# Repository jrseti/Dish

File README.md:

# Dish Repository

This repository contains hardware and firmware work for refurbishing a legacy
3-meter satellite dish into a modern, networked robotic system.

The design is split into two PCB projects that work together over CAN:

## Projects

### 1. `controller/` - RCM Dish Controller Board

The main motion-control and compute board for the dish.

- STM32-based two-axis motion controller
- On-board Raspberry Pi Compute Module 4 carrier
- Power, I/O, communications, and safety/control interfaces
- KiCad hardware design plus associated embedded/software assets

See: [controller/README.md](controller/README.md)

### 2. `can_hub/` - CAN Bus Hub

A simple CAN distribution hub that also routes 24 V power to CAN_V+ pins.

See: [can_hub/README.md](can_hub/README.md)

## Repository Layout

- `controller/`: Main controller electronics, docs, and software
- `can_hub/`: CAN power/distribution hub hardware

## Purpose

Together, these boards provide the control and field-bus backbone for the dish:

- `controller/` runs motion control and local host integration
- `can_hub/` provides CAN/power fan-out for connected nodes

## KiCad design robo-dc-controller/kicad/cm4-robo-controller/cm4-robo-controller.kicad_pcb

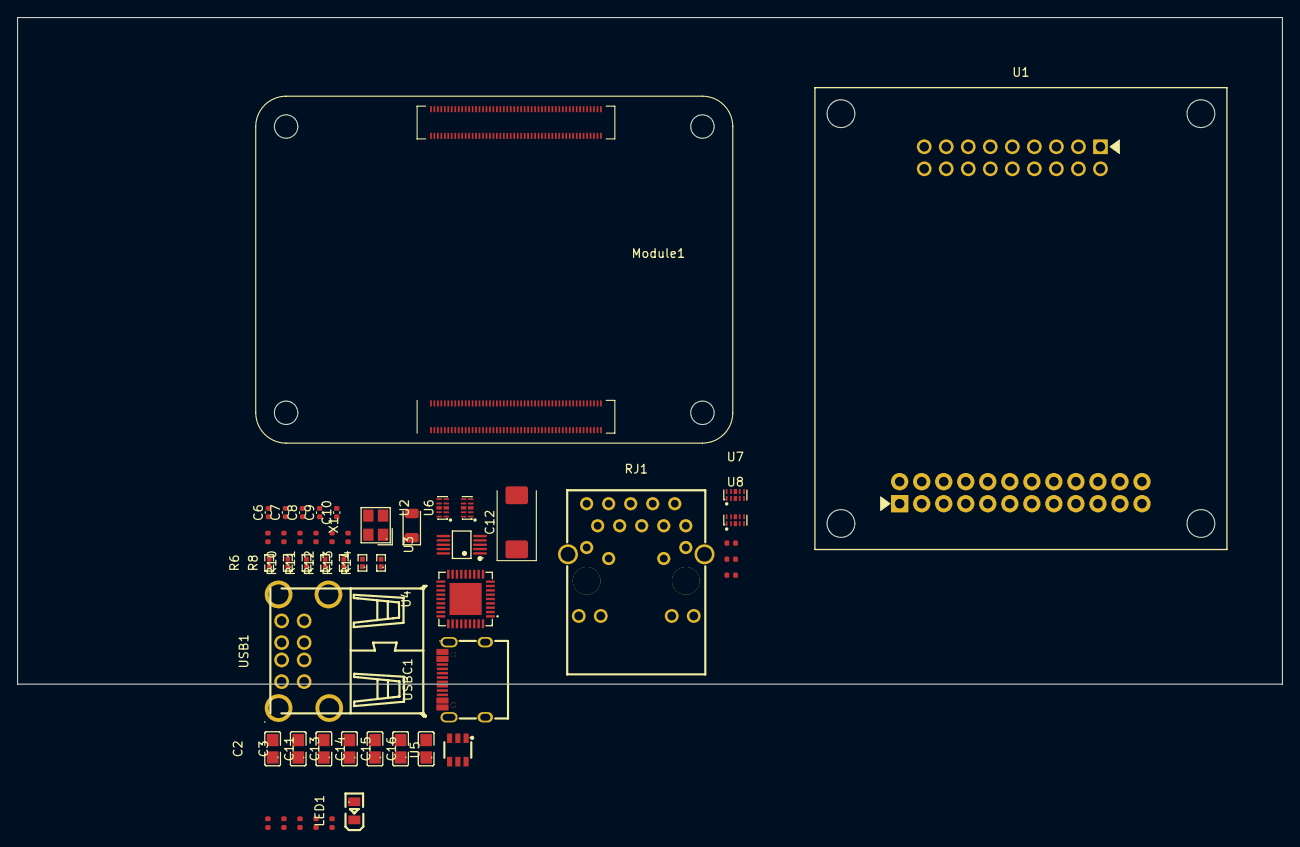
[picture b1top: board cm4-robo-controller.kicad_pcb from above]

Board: 2 copper layers, 145.8 x 76.9 mm, 49 parts (0 on the bottom side), 48 nets, no tracks yet.

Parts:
C1, C4: 15pF; C_0402
C2, C3, C11, C13, C14, C15, C16: 10uF 10V; C0805
C5, C17: 100nF; C_0402
C6, C7, C8, C9, C10: 100n; C_0402_1005Metric
C12: 100uF 6.3V; CP_EIA-7343-31_Kemet-D
D1: SMF6.0A; D_SOD-123FL
LED1: RED; LED0805-R-RD
Module1: ComputeModule4-CM4; Raspberry-Pi-4-Compute-Module
R1: 10kΩ; R_0402
R2, R3, R4: 100Ω; R_0402
R5, R16, R17: 1.5kΩ; R_0402
R6, R8: 2.2kΩ; R0402
R7, R9: 5.1kΩ; R_0402
R10, R11, R13, R14: 36K 1%; R0402
R12: 12kΩ; R0402
R15: 15kΩ; R_0402
RJ1: LPJG0926HENL_C22457393; RJ45-TH_LPJG0926HENL_C22457393
U1: ROBOCLAW-2X15A-OEM; MOD-TH_ROBOCLAW-OEM-2X15A
U2, U6: TPD4EUSB30DQAR-N; DFN-10_L2.5-W1.0-P0.50-BL-A
U3: FSUSB42MUX; MSOP-10_L3.0-W3.0-P0.50-LS5.0-BL
U4: USB2514B-I/M2; SQFN-36_L6.0-W6.0-P0.50-BL-EP
U5: AP22653W6-7; SOT-23-6_L2.9-W1.6-P0.95-LS2.8-BR
U7, U8: TPD4EUSB30DQAR; USON-10_L2.5-W1.0-P0.50-BL
USB1: Double layer DIP 90° black; USB-A-TH_USB-M-51
USBC1: TYPE-C-31-M-12; USB-C_SMD-TYPE-C-31-M-12_1
X1: X322524MOB4SI; CRYSTAL-SMD_4P-L3.2-W2.5-BL

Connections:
3V3_CM4: C2.2, C3.2, C5.1, C6.1, C7.1, C8.1, C9.1, C10.1, Module1.78 (GPIO_VREF(1.8v/3.3v_Input)), Module1.84 (+3.3v_(Output)), Module1.86 (+3.3v_(Output)), R1.1, U3.1 (VCC), U4.5 (VDDA33), U4.10 (VDDA33), U4.15 (VDD33), U4.23 (VDD33), U4.27 (VBUS_DET), U4.29 (VDDA33), U4.36 (VDDA33)
5V: C11.2, LED1.1 (A), Module1.77 (+5v_(Input)), Module1.79 (+5v_(Input)), Module1.81 (+5v_(Input)), Module1.83 (+5v_(Input)), Module1.85 (+5v_(Input)), Module1.87 (+5v_(Input)), RJ1.15, RJ1.17, U5.1 (IN)
/CM4/EP0+: Module1.12 (Ethernet_Pair0_P), RJ1.1 (TD1+), U7.1 (D1+)
/CM4/EP0-: Module1.10 (Ethernet_Pair0_N), RJ1.2 (TD1-), U7.2 (D1-)
/CM4/EP1+: Module1.4 (Ethernet_Pair1_P), RJ1.3 (TD2+), U7.4 (D2+)
/CM4/EP1-: Module1.6 (Ethernet_Pair1_N), RJ1.6 (TD2-), U7.5 (D2-)
/CM4/EP2+: Module1.11 (Ethernet_Pair2_P), RJ1.7 (TD3+), U8.1 (D1+)
/CM4/EP2-: Module1.9 (Ethernet_Pair2_N), RJ1.8 (TD3-), U8.2 (D1-)
/CM4/EP3+: Module1.3 (Ethernet_Pair3_P), RJ1.9 (TD4+), U8.4 (D2+)
/CM4/EP3-: Module1.5 (Ethernet_Pair3_N), RJ1.10 (TD4-), U8.5 (D2-)
/CM4/ETH_LEDG: Module1.17 (Ethernet_nLED2(3.3v)), R16.1
/CM4/ETH_LEDY: Module1.15 (Ethernet_nLED3(3.3v)), R17.2
/CM4/MCU_nIRQ: R1.2, R2.1
/CM4/USB2_N: Module1.103 (USB2_N), U3.4 (D-)
/CM4/USB2_P: Module1.105 (USB2_P), U3.3 (D+)
/CM4/USB_OTG_ID: Module1.101 (USB_OTG_ID), R6.1, R8.1, U3.2 (Sel)
/CM4/nEXTRST: Module1.100 (nEXTRST), U4.26 (RESET_N)
/CM4/usb/HD1_N: U4.1 (USBDM_DN1/PRT_DIS_M1), U6.5, USB1.6 (D-)
/CM4/usb/HD1_P: U4.2 (USBDP_DN1/PRT_DIS_P1), U6.4, USB1.7 (D+)
/CM4/usb/HD2_N: U4.3 (USBDM_DN2/PRT_DIS_M2), U6.2, USB1.2 (D-)
/CM4/usb/HD2_P: U4.4 (USBDP_DN2/PRT_DIS_P2), U6.1, USB1.3 (D+)
/CM4/usb/HSD2+: U2.1, U3.9 (HSD2+), USBC1.A6 (DP1), USBC1.B6 (DP2)
/CM4/usb/HSD2-: U2.2, U3.8 (HSD2-), USBC1.A7 (DN1), USBC1.B7 (DN2)
/CM4/usb/PWR1: U4.12 (PRTPWR1/BC_EN1), U5.3 (EN/~EN)
/CM4/usb/VBUS: C12.1, C13.2, C14.2, C15.2, C16.2, D1.1, U5.6 (OUT), USB1.1 (VCC), USB1.5 (VCC)
/CM4/usb/nOCS1: U4.13 (OCS_N1), U4.17 (OCS_N2), U4.19 (OCS_N3), U4.21 (OCS_N4), U5.4 (~FAULT)
GND: C1.2, C2.1, C3.1, C4.2, C5.2, C6.2, C7.2, C8.2, C9.2, C10.2, C11.1, C12.2, C13.1, C14.1, C15.1, C16.1, C17.2, D1.2, Module1.1 (GND), Module1.2 (GND), Module1.7 (GND), Module1.8 (GND), Module1.13 (GND), Module1.14 (GND), Module1.22 (GND), Module1.23 (GND), Module1.32 (GND), Module1.33 (GND), Module1.42 (GND), Module1.43 (GND), Module1.52 (GND), Module1.53 (GND), Module1.59 (GND), Module1.60 (GND), Module1.65 (GND), Module1.66 (GND), Module1.71 (GND), Module1.74 (GND), Module1.98 (GND), Module1.107 (GND), Module1.108 (GND), Module1.113 (GND), Module1.114 (GND), Module1.119 (GND), Module1.120 (GND), Module1.125 (GND), Module1.126 (GND), Module1.131 (GND), Module1.132 (GND), Module1.137 (GND), Module1.138 (GND), Module1.144 (GND), Module1.150 (GND), Module1.155 (GND), Module1.156 (GND), Module1.161 (GND), Module1.162 (GND), Module1.167 (GND), Module1.168 (GND), Module1.173 (GND), Module1.174 (GND), Module1.179 (GND), Module1.180 (GND), Module1.185 (GND), Module1.186 (GND), Module1.191 (GND), Module1.192 (GND), Module1.197 (GND), Module1.198 (GND), R6.2, R7.2, R9.2, R10.1, R11.1, R12.1, R13.1, R14.1, R15.2, RJ1.19 (EH), RJ1.20 (EH), U2.3, U2.8, U3.5 (GND), U3.10 (~OE), U4.37 (EP), U5.2 (GND), U6.3, U6.8, U7.3 (GND), U7.8 (GND), U8.3 (GND), U8.8 (GND), USB1.4 (GND), USB1.8 (GND), USB1.9, USBC1.1 (EH), USBC1.2 (EH), USBC1.3 (EH), USBC1.4 (EH), USBC1.A1B12 (GND), USBC1.B1A12 (GND), X1.2 (GND), X1.4 (GND)
unnamed: C17.1, RJ1.4 (CT), RJ1.5 (CT)
unnamed: LED1.2 (K), R5.1
unnamed: Module1.54 (GPIO4), R4.2
unnamed: Module1.34 (GPIO5), R3.2
unnamed: Module1.30 (GPIO6), R2.2
unnamed: Module1.21 (PI_nLED_Activity), R5.2
unnamed: R8.2, USBC1.A4B9 (VBUS), USBC1.B4A9 (VBUS)
unnamed: R16.2, RJ1.16
unnamed: R17.1, RJ1.18
unnamed: U3.7 (HSD1+), U4.31 (USBDP_UP)
unnamed: U3.6 (HSD1-), U4.30 (USBDM_UP)
unnamed: R14.2, U4.25 (HS_IND/CFG_SEL1)
unnamed: R12.2, U4.35 (RBIAS)
unnamed: R10.2, U4.24 (SCL/SMBCLK/CFG_SEL0)
unnamed: R11.2, U4.22 (SDA/SMBBATA/NON_REM1)
unnamed: R13.2, U4.28 (SUSP_IND/LOCAL_PWR/NON_REM0)
unnamed: C1.1, U4.33 (XTALIN/CLKIN), X1.1 (OSC1)
unnamed: C4.1, U4.32 (XTALOUT), X1.3 (OSC2)
unnamed: R15.1, U5.5 (ILIM)
unnamed: R7.1, USBC1.A5 (CC1)
unnamed: R9.1, USBC1.B5 (CC2)

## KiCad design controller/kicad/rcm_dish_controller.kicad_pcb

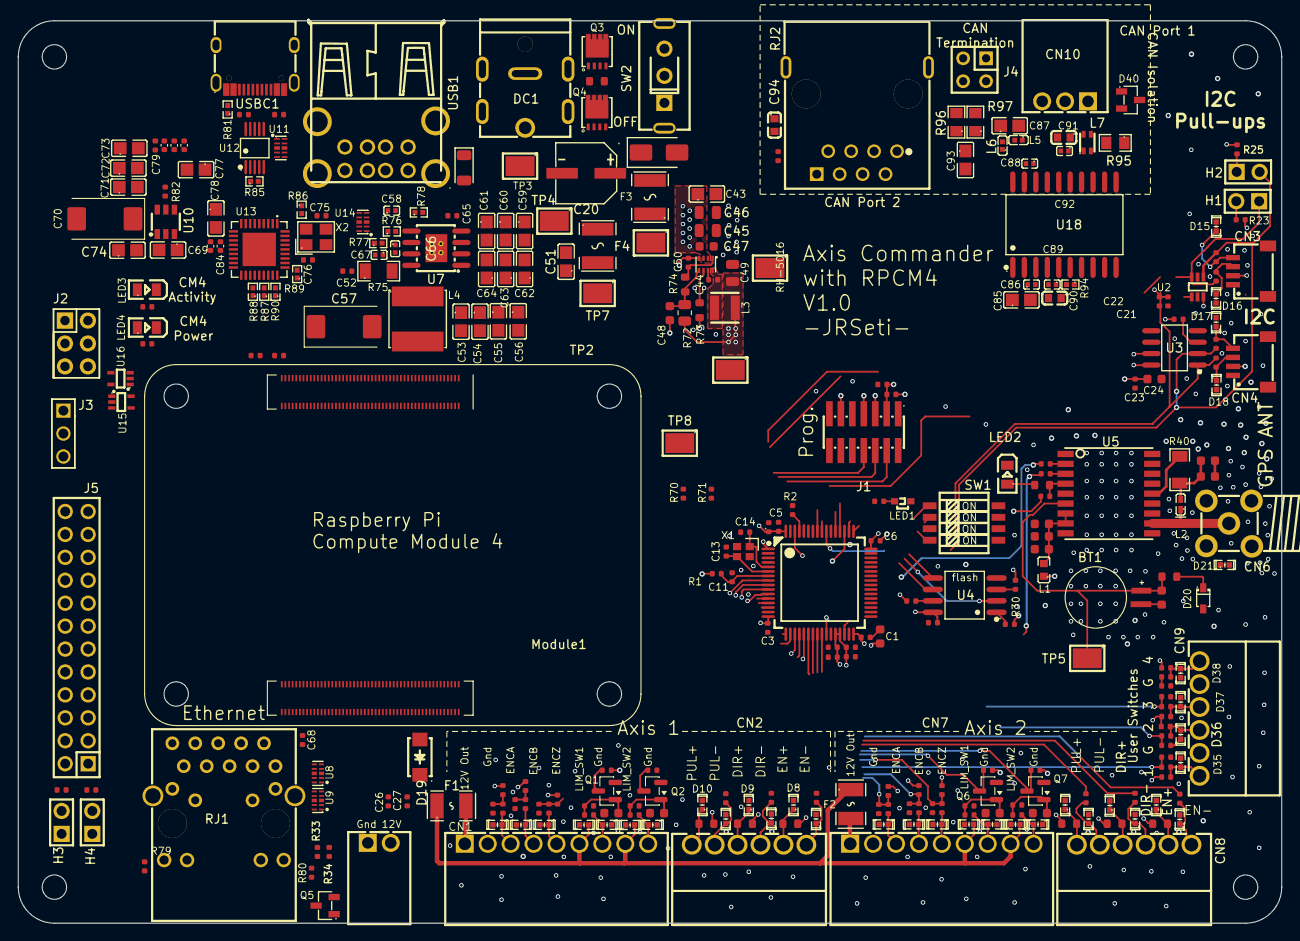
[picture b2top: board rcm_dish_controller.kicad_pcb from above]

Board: 4 copper layers, 140.0 x 100.0 mm, 314 parts (0 on the bottom side), 205 nets.

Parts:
BT1: MS621FE-FL11E; BAT_MS621FE-FL11E
C1: 4.7uF; C_0603
C2, C3, C4, C5, C6, C9, C11, C12, C12#2, C22, C23, C25, C27, C39, C40, C41, C42, C44, C52, C65, C68, C79: 100nF; C_0402
C7, C26: 10nF; C_0402
C8, C10, C50: 1uF; C_0402
C13, C14: 6.8pF; C_0402
C15, C16, C17, C34, C35, C36: 1nF; C_0402
C18, C19, C33, C37, C38: 10nF; C_0603
C20: 220uF; CAP-SMD_BD6.3-L6.6-W6.6-FD
C21: 4.7uF; C_0402
C24, C29: 10uF; C_0603
C28: 1uF; C_0603
C30, C31, C47: 100nF; C_0603
C32: 47pF; C_0603
C43, C51: 100nF; C0805
C45, C46: 10uF; C_0805
C48: 22pF; C_0603
C49: 22uF; C_0805
C53, C54, C55, C56, C69, C71, C72, C73, C74, C77, C78: 10uF 10V; C0805
C57, C70: 100uF 6.3V; CP_EIA-7343-31_Kemet-D
C58, C66: DNP; C0402
C59, C60, C61, C62, C63, C64: 10uF 35V; C0805
C67: 1.2nF; C0402
C75, C76: 15pF; C_0402
C80, C81, C82, C83, C84: 100n; C_0402_1005Metric
C85, C87: 10uF; C0805
C86, C88, C89, C92: 100nF; C0402
C90, C91: 10nF; C0603
C93: 4.7nF; C0805
C94: 1nF; C0603
CN1, CN7: KF2EDGR-2.54-9P; CONN-TH_9P-P2.54_KF2EDGR-2.54-9P
CN2, CN8, CN9: KF2EDGR-2.54-6P; CONN-TH_KF2EDGR-2.54-6P
CN3, CN4: SM04B-SRSS-TB (LF)(SN); CONN-SMD_4P-P1.00_SM04B-SRSS-TB-LF-SN
CN5: KF2EDGR-2.54-2P; CONN-TH_P2.54_KF2EDGR-2.54-2P
CN6: SMA-KWE_C7498154; SMA-TH_SMA-KWE_C7498154
CN10: KF2EDGR-2.54-3P; CONN-TH_3P-P2.54_KF2EDGR-2.54-3P
D1, D2, D3, D8, D9, D10, D11, D12, D13, D15, D16, D17, D18, D22, D23, D24, D29, D30, D31, D32, D33, D34, D35, D36, D37, D38: TPESD0402G05V; D0402-BI
D4, D5, D6, D7, D25, D26, D27, D28: TPESD0402G15V; D0402-BI
D14: SMAJ14A; D_SMA
D19: SS14; SMA_L4.2-W2.6-LS5.0-RD_1
D20: 1N4148WS T4; SOD-323_L1.8-W1.3-LS2.5-RD
D21: PESD0402-140; D0402-BI
D39: SMF6.0A; D_SOD-123FL
D40: NUP2105LT1G; SOT-23-3_L2.9-W1.3-P1.90-LS2.4-BL-2
DC1: DC007B-2.5-J; DC-IN-TH_HX-DC007B-2.5
F1, F2: MF-USMF020-2; F1210
F3: 1812L110/48QR; F1812
F4: SMD1812P300TF/16; F1812
H1, H2, H3, H4: 210S-1*2P L=11.6MMGold-plated black; HDR-TH_2P-P2.54-V-M-1
J1: Conn_ST_STDC14; HDR-SMD_14P-P1.27_FTSH-107-01-L-DV-K
J2: Header-Male-2.54_2x3; HDR-TH_6P-P2.54-V-M-R2-C3-S2.54-1
J3: Header-Male-2.54_1x3; HDR-TH_3P-P2.54-V-M-1
J4: Header-Male-2.54_2x2; HDR-TH_4P-P2.54-V-M-R2-C2-S2.54-1
J5: 2541WV-2X12P; HDR-TH_24P-P2.54-V-M-R2-C12-S2.54
L1: BLM18AG601SN1D; L0603
L2: LQG15HS27NJ02D; L0402-RD
L3: 3.3uH; IND-SMD_L3.0-W3.0-1
L4: SRN6045TA-3R3Y; IND-SMD_L6.0-W6.0
L5, L6: BLM15HD182SN1D; L0402
L7: 370R@100MHz; FILTER-SMD_4P-L2.0-W1.2-BL
LED1: LTST-S270KGKT; LED-SMD_L1.7-W0.6-RD
LED2: XL-0805QBC; LED0805-R-RD
LED3: RED; LED0805-R-RD
LED4: GREEN; LED0805-R-RD
M1, M2, M3, M4: MountingHole_2.7mm_M2.5_ISO14580
Module1: ComputeModule4-CM4; Raspberry-Pi-4-Compute-Module
Q1, Q2, Q6, Q7: BSS138; SOT-23
Q3, Q4: DMP3013SFV-7; DFN-8_L3.3-W3.3-P0.65-BL
Q5: AO3400A; SOT-23-3_L2.9-W1.3-P1.90-LS2.4-BR
R1, R2, R13, R14, R18, R19, R23, R24, R25, R26, R27, R30, R34, R49, R50, R55, R56, R68: 10kΩ; R_0402
R3: 330Ω; R_0402
R4, R5, R6, R38, R41, R42, R43, R91: 1kΩ; R_0402
R7, R8, R9, R11, R15, R17, R33, R35, R36, R44, R45, R46, R48, R52, R54, R60, R62, R64, R66, R69, R70, R71: 100Ω; R_0402
R10, R12, R16, R47, R51, R53: 180Ω; R_0603
R20, R21, R57, R58, R82: 15kΩ; R_0402
R22: 10kΩ; R_0603
R28, R29, R31, R32: 22Ω; R_0402
R37, R39: 1kΩ; R_0603
R40, R75: 10Ω; R1206
R59, R61, R63, R65, R92, R93: 4.7kΩ; R_0402
R67, R79, R80: 1.5kΩ; R_0402
R72: 976kΩ; R_0805_2012Metric
R73: 100kΩ; R_0603
R74: 220kΩ; R_0603
R76, R86: 12kΩ; R0402
R77: 20kΩ; R0402
R78, R81, R85: 2.2kΩ; R0402
R83, R84: 5.1kΩ; R_0402
R87, R88, R89, R90: 36K 1%; R0402
R94: 0Ω; R0402
R95: 47KΩ; R0805
R96, R97: 60.4Ω; R0805
R98: 1MΩ; R_0402
RJ1: LPJG0926HENL_C22457393; RJ45-TH_LPJG0926HENL_C22457393
RJ2: KH-RJ45-58-8P8C; RJ45-TH_KH-RJ45-58-8P8C
SW1: DSHP04TSGER; SW-SMD_8P-L6.7-W5.4-P1.27-LS8.4
SW2: SS-12F49-G050; SW-TH_SS-12F45-GXXX
TP1, TP2, TP3, TP4, TP5, TP6, TP7, TP8: RH-5016; TESTPOINT-SMD_L3.0-W2.0
U1: STM32G474RET6; LQFP-64_L10.0-W10.0-P0.50-LS12.0-BL
U2: LTC4311ISC6#TRPBF; SC-70-6_L2.2-W1.3-P0.65-LS2.2-BL
U3: LM75BIMX-3/NOPB; SOIC-8_L4.9-W3.9-P1.27-LS6.0-BL
U4: W25Q32JVSSIQ_C179173; SOIC-8_L5.3-W5.3-P1.27-LS8.0-BL
U5: MAX-M10S-00B; SMD-18_L10.1-W9.7-P1.10-TL_SKG09F
U6: MP2322GQH-Z; QFN-8_L2.0-W1.5-P0.50-BL
U7: AP64501SP-13; SOIC-8_L4.9-W3.9-P1.27-LS6.0-BL-EP-1
U8, U9: TPD4EUSB30DQAR; USON-10_L2.5-W1.0-P0.50-BL
U10: AP22653W6-7; SOT-23-6_L2.9-W1.6-P0.95-LS2.8-BR
U11, U14: TPD4EUSB30DQAR-N; DFN-10_L2.5-W1.0-P0.50-BL-A
U12: FSUSB42MUX; MSOP-10_L3.0-W3.0-P0.50-LS5.0-BL
U13: USB2514B-I/M2; SQFN-36_L6.0-W6.0-P0.50-BL-EP
U15, U16: 74LVC1G07SE-7; SC-88A_L2.0-W1.3-P0.65-LS2.1-BL
U18: ADM3057EBRWZ-RL; SOIC-20_L13.0-W7.6-P1.27-LS10.3-BL
USB1: Double layer DIP 90° black; USB-A-TH_USB-M-51
USBC1: TYPE-C-31-M-12; USB-C_SMD-TYPE-C-31-M-12_1
X1: NX2016SA-16MHZ-EXS00A-CS07826; CRYSTAL-SMD_4P-L2.0-W1.6-BL
X2: X322524MOB4SI; CRYSTAL-SMD_4P-L3.2-W2.5-BL

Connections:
3V3: C1.1, C2.1, C3.1, C4.1, C5.1, C6.1, C7.1, C8.1, C9.1, C10.1, C12.1, C12#2.1, C21.1, C22.1, C23.1, C24.1, C25.1, C48.1, C49.1, C89.2, C90.2, CN3.2, CN4.2, D20.2 (A), J1.3 (VCC), L1.1, L3.2, R1.1, R4.1, R5.1, R6.1, R10.1, R12.1, R13.1, R14.1, R16.1, R23.1, R24.2, R25.1, R26.1, R27.1, R30.1, R41.1, R42.1, R43.1, R47.1, R49.1, R50.1, R51.1, R53.1, R59.1, R61.1, R63.1, R65.1, R72.1, TP1.1 (1_1), U1.1 (VBAT), U1.16 (VDD), U1.28 (VREF+), U1.29 (VDDA), U1.32 (VDD), U1.48 (VDD), U1.64 (VDD), U2.1 (VCC), U2.3 (ENABLE), U3.7 (A0), U3.8 (+VS), U4.8 (VCC), U15.5 (VCC), U18.4 (VIO)
3V3_CM4: C77.2, C78.2, C79.1, C80.1, C81.1, C82.1, C83.1, C84.1, J5.7, LED4.1 (A), Module1.78 (GPIO_VREF(1.8v/3.3v_Input)), Module1.84 (+3.3v_(Output)), Module1.86 (+3.3v_(Output)), R68.1, R92.1, R93.1, U12.1 (VCC), U13.5 (VDDA33), U13.10 (VDDA33), U13.15 (VDD33), U13.23 (VDD33), U13.27 (VBUS_DET), U13.29 (VDDA33), U13.36 (VDDA33), U16.5 (VCC)
5V: C53.2, C54.2, C55.2, C56.2, C57.1, C58.1, C69.2, C85.2, C86.2, J5.5, L4.2, LED3.1 (A), Module1.77 (+5v_(Input)), Module1.79 (+5v_(Input)), Module1.81 (+5v_(Input)), Module1.83 (+5v_(Input)), Module1.85 (+5v_(Input)), Module1.87 (+5v_(Input)), R76.1, RJ1.15, RJ1.17, TP8.1 (1_1), U10.1 (IN), U18.3 (VCC)
12V: C20.1, C26.1, C27.1, CN1.6, CN1.8, CN5.1, CN7.6, CN7.8, D4.2, D6.2, D14.1, D19.1 (K), D25.2, D27.2, F1.1, F2.1, F3.1, F4.1, Q4.5 (D), TP4.1 (1_1)
/1PPS_MCU: Module1.29 (GPIO16), R38.1, U1.62 (PB9)
/Axis Control - 1/12VENC: CN1.1, F1.2
/Axis Control - 1/ENC1_A: CN1.3, D1.1 (K), R7.1
/Axis Control - 1/ENC1_B: CN1.4, D2.1 (K), R8.1
/Axis Control - 1/ENC1_Z: CN1.5, D3.1 (K), R9.1
/Axis Control - 1/LIM1_SW1_RETURN: CN1.7, D5.2, R18.2
/Axis Control - 1/LIM1_SW2_RETURN: CN1.9, D7.2, R19.2
/Axis Control - 2/12VENC: CN7.1, F2.2
/Axis Control - 2/DIR2+: CN8.3, D30.1 (K), R51.2
/Axis Control - 2/DIR2-: CN8.4, D33.1 (K), R52.2
/Axis Control - 2/ENABLE2+: CN8.5, D29.1 (K), R53.2
/Axis Control - 2/ENABLE2-: CN8.6, D34.1 (K), R54.2
/Axis Control - 2/ENC2_A: CN7.3, D22.1 (K), R44.1
/Axis Control - 2/ENC2_B: CN7.4, D23.1 (K), R45.1
/Axis Control - 2/ENC2_Z: CN7.5, D24.1 (K), R46.1
/Axis Control - 2/LIM2_SW1_RETURN: CN7.7, D26.2, R55.2
/Axis Control - 2/LIM2_SW2_RETURN: CN7.9, D28.2, R56.2
/Axis Control - 2/PUL2+: CN8.1, D31.1 (K), R47.2
/Axis Control - 2/PUL2-: CN8.2, D32.1 (K), R48.2
/CAN/CANH: CN10.2, D40.1, J4.1, L7.4, RJ2.1
/CAN/CANHL_C: C93.1, R96.1, R97.1
/CAN/CANH_T: J4.2, R97.2
/CAN/CANL: CN10.1, D40.2, J4.3, L7.3, RJ2.2
/CAN/CANL_T: J4.4, R96.2
/CAN/CAN_SHLD: C94.2, R98.1, RJ2.9, RJ2.10
/CAN/CH: L7.1, U18.14 (CANH)
/CAN/CL: L7.2, U18.13 (CANL)
/CAN/RS: R95.2, U18.12 (RS)
/CAN/RXD: R94.2, U18.5 (RXD)
/CAN/VISOIN: C87.2, C91.2, C92.2, L5.2, U18.16 (VISOIN)
/CAN_RX: R94.1, U1.45 (PA11)
/CAN_TX: U1.46 (PA12), U18.7 (TXD)
/CM4_RX: R71.1, U1.60 (PB7)
/CM4_TX: R70.1, U1.59 (PB6)
/DIR1_MCU: R15.1, U1.22 (PC4)
/DIR2_MCU: R52.1, U1.25 (PB1)
/ENABLE1_MCU: R17.1, U1.23 (PC5)
/ENABLE2_MCU: R54.1, U1.26 (PB2)
/ENC1_A_MCU: C15.1, R4.2, R7.2, U1.12 (PA0)
/ENC1_B_MCU: C16.1, R5.2, R8.2, U1.13 (PA1)
/ENC1_Z_MCU: C17.1, R6.2, R9.2, U1.14 (PA2)
/ENC2_A_MCU: C34.1, R41.2, R44.2, U1.8 (PC0)
/ENC2_B_MCU: C35.1, R42.2, R45.2, U1.9 (PC1)
/ENC2_Z_MCU: C36.1, R43.2, R46.2, U1.11 (PC3)
/FAN_MCU: R33.1, R34.1, U1.57 (PB4)
/FLASH_CS_MCU: R26.2, U1.34 (PB12), U4.1 (~CS)
/GPS/RF_IN: CN6.5, D21.2, L2.1, U5.11 (RF_IN)
/GPS/TIMEPULSE: R38.2, R39.1, U5.4 (TIMEPULSE)
/GPS/VCC: C29.1, C30.1, C31.1, L1.2, U5.7 (V_IO), U5.8 (VCC)
/GPS/VCC_RF: R40.2, U5.14 (VCC_RF)
/GPS/V_BCKP: BT1.+, C28.1, R37.2, TP5.1 (1_1), U5.6 (V_BCKP)
/GPS_RX_MCU: R35.1, U1.30 (PB10)
/GPS_TX_MCU: R36.1, U1.33 (PB11)
/I2C and EEPROM/OS: R24.1, U3.3 (OS)
/I2C and EEPROM/SCL: CN3.4, D15.1 (K), R28.2
/I2C and EEPROM/SDA: CN3.3, D16.1 (K), R31.2
/LIMIT1_SW1_MCU: Q1.3 (D), R13.2, U1.17 (PA3)
/LIMIT1_SW2_MCU: Q2.3 (D), R14.2, U1.18 (PA4)
/LIMIT2_SW1_MCU: Q6.3 (D), R49.2, U1.19 (PA5)
/LIMIT2_SW2_MCU: Q7.3 (D), R50.2, U1.21 (PA7)
/MCU_nIRQ: R68.2, R69.1, U1.55 (PD2)
/NRST: C11.1, J1.12 (~RST), R1.2, U1.7 (PG10-NRST)
/OSC_IN: C14.2, U1.5 (PF0-OSC_IN), X1.1
/OSC_OUT: C13.1, U1.6 (PF1-OSC_OUT), X1.3
/PUL1_MCU: R11.1, U1.20 (PA6)
/PUL2_MCU: R48.1, U1.24 (PB0)
/Power/12V_IN: DC1.1, Q3.5 (D), TP3.1 (1_1)
/Power/Power_3V3/12V_MCU: C43.1, C45.1, C46.1, C47.1, F3.2, TP6.1 (1_1), U6.2 (IN), U6.3 (EN)
/Power/Power_5V/12V_CM4: C51.1, C59.2, C60.2, C61.2, C62.2, C63.2, C64.2, F4.2, TP7.1 (1_1), U7.2 (VIN), U7.3 (EN)
/RCM4/AIN0: J5.2, Module1.96 (AnalogIP0)
/RCM4/AIN1: J5.4, Module1.94 (AnalogIP1)
/RCM4/BOOT_CONSOLE_RXD: J3.1, Module1.51 (GPIO15)
/RCM4/BOOT_CONSOLE_TXD: J3.2, Module1.55 (GPIO14)
/RCM4/EEPROM_nWP: J2.4, Module1.20 (EEPROM_nWP)
/RCM4/EP0+: Module1.12 (Ethernet_Pair0_P), RJ1.1 (TD1+), U8.1 (D1+)
/RCM4/EP0-: Module1.10 (Ethernet_Pair0_N), RJ1.2 (TD1-), U8.2 (D1-)
/RCM4/EP1+: Module1.4 (Ethernet_Pair1_P), RJ1.3 (TD2+), U8.4 (D2+)
/RCM4/EP1-: Module1.6 (Ethernet_Pair1_N), RJ1.6 (TD2-), U8.5 (D2-)
/RCM4/EP2+: Module1.11 (Ethernet_Pair2_P), RJ1.7 (TD3+), U9.1 (D1+)
/RCM4/EP2-: Module1.9 (Ethernet_Pair2_N), RJ1.8 (TD3-), U9.2 (D1-)
/RCM4/EP3+: Module1.3 (Ethernet_Pair3_P), RJ1.9 (TD4+), U9.4 (D2+)
/RCM4/EP3-: Module1.5 (Ethernet_Pair3_N), RJ1.10 (TD4-), U9.5 (D2-)
/RCM4/ETH_LEDG: Module1.17 (Ethernet_nLED2(3.3v)), R79.1
/RCM4/ETH_LEDY: Module1.15 (Ethernet_nLED3(3.3v)), R80.2
/RCM4/GLOBAL_EN: J2.6, Module1.99 (Global_EN)
/RCM4/GPIO22: J5.24, Module1.46 (GPIO22)
/RCM4/I2C1_SCL: H4.1, J5.18, Module1.56 (GPIO3)
/RCM4/I2C1_SDA: H3.1, J5.16, Module1.58 (GPIO2)
/RCM4/PWM0: J5.20, Module1.31 (GPIO12)
/RCM4/PWM1: J5.22, Module1.28 (GPIO13)
/RCM4/RUN_PG: Module1.92 (RUN_PG), U15.2 (A)
/RCM4/SPI0_CE0: J5.12, Module1.39 (GPIO8)
/RCM4/SPI0_CE1: J5.14, Module1.37 (GPIO7)
/RCM4/SPI0_MISO: J5.10, Module1.40 (GPIO9)
/RCM4/SPI0_MOSI: J5.8, Module1.44 (GPIO10)
/RCM4/SPI0_SCLK: J5.6, Module1.38 (GPIO11)
/RCM4/USB2_N: Module1.103 (USB2_N), U12.4 (D-)
/RCM4/USB2_P: Module1.105 (USB2_P), U12.3 (D+)
/RCM4/USB_OTG_ID: Module1.101 (USB_OTG_ID), R81.1, R85.1, U12.2 (Sel)
/RCM4/nEXTRST: Module1.100 (nEXTRST), U13.26 (RESET_N)
/RCM4/nPWR_LED: Module1.95 (nPI_LED_PWR), U16.2 (A)
/RCM4/nRPIBOOT: J2.2, Module1.93 (nRPIBOOT)
/RCM4/usb/HD1_N: U13.1 (USBDM_DN1/PRT_DIS_M1), U14.5, USB1.6 (D-)
/RCM4/usb/HD1_P: U13.2 (USBDP_DN1/PRT_DIS_P1), U14.4, USB1.7 (D+)
/RCM4/usb/HD2_N: U13.3 (USBDM_DN2/PRT_DIS_M2), U14.2, USB1.2 (D-)
/RCM4/usb/HD2_P: U13.4 (USBDP_DN2/PRT_DIS_P2), U14.1, USB1.3 (D+)
/RCM4/usb/HSD2+: U11.1, U12.9 (HSD2+), USBC1.A6 (DP1), USBC1.B6 (DP2)
/RCM4/usb/HSD2-: U11.2, U12.8 (HSD2-), USBC1.A7 (DN1), USBC1.B7 (DN2)
/RCM4/usb/PWR1: U10.3 (EN/~EN), U13.12 (PRTPWR1/BC_EN1)
/RCM4/usb/VBUS: C70.1, C71.2, C72.2, C73.2, C74.2, D39.1, U10.6 (OUT), USB1.1 (VCC), USB1.5 (VCC)
/RCM4/usb/nOCS1: U10.4 (~FAULT), U13.13 (OCS_N1), U13.17 (OCS_N2), U13.19 (OCS_N3), U13.21 (OCS_N4)
/SCL_MCU: H2.2, R28.1, R29.1, U1.38 (PC6), U2.4 (BUS2), U3.2 (SCL)
/SDA_MCU: H1.1, R31.1, R32.1, U1.39 (PC7), U2.6 (BUS1), U3.1 (SDA)
/SPI2_MISO_MCU: U1.36 (PB14), U4.2 (DO(IO1))
/SPI2_MOSI_MCU: U1.37 (PB15), U4.5 (DI(IO0))
/SPI2_SCK_MCU: U1.35 (PB13), U4.6 (CLK)
/STATUS_LED: R3.1, U1.53 (PC11)
/SW1: SW1.1 (A1), U1.52 (PC10)
/SW2: SW1.2 (A2), U1.44 (PA10)
/SW3: SW1.3 (A3), U1.43 (PA9)
/SW4: SW1.4 (A4), U1.42 (PA8)
/SWCLK: J1.6 (JCLK/SWCLK), U1.50 (PA14)
/SWDIO: J1.4 (JTMS/SWDIO), U1.49 (PA13)
/SWO: J1.8 (JTDO/SWO), U1.56 (PB3)
/USER_SW_1_MCU: C39.1, R60.2, U1.10 (PC2)
/USER_SW_2_MCU: C40.1, R62.2, U1.40 (PC8)
/USER_SW_3_MCU: C41.1, R64.2, U1.41 (PC9)
/USER_SW_4_MCU: C42.1, R66.2, U1.51 (PA15)
/User Switches/USER_SW_1: CN9.1, D35.1 (K), R59.2, R60.1
/User Switches/USER_SW_2: CN9.3, D36.1 (K), R61.2, R62.1
/User Switches/USER_SW_3: CN9.4, D37.1 (K), R63.2, R64.1
/User Switches/USER_SW_4: CN9.6, D38.1 (K), R65.2, R66.1
CAN_GND: C87.1, C91.1, C92.1, C93.2, C94.1, CN10.3, D40.3, L6.2, R95.1, R98.2, RJ2.3, U18.11 (GND2), U18.15 (GND2)
CAN_GNDISO: C88.1, L6.1, U18.18 (GNDISO), U18.20 (GNDISO)
GND: BT1.-, C1.2, C2.2, C3.2, C4.2, C5.2, C6.2, C7.2, C8.2, C9.2, C10.2, C11.2, C12.2, C12#2.2, C13.2, C14.1, C15.2, C16.2, C17.2, C18.2, C19.2, C20.2, C21.2, C22.2, C23.2, C24.2, C25.2, C26.2, C27.2, C28.2, C29.2, C30.2, C31.2, C32.2, C33.2, C34.2, C35.2, C36.2, C37.2, C38.2, C39.2, C40.2, C41.2, C42.2, C43.2, C45.2, C46.2, C47.2, C49.2, C50.2, C51.2, C53.1, C54.1, C55.1, C56.1, C57.2, C59.1, C60.1, C61.1, C62.1, C63.1, C64.1, C65.2, C66.2, C67.1, C68.2, C69.1, C70.2, C71.1, C72.1, C73.1, C74.1, C75.2, C76.2, C77.1, C78.1, C79.2, C80.2, C81.2, C82.2, C83.2, C84.2, C85.1, C86.1, C89.1, C90.1, CN1.2, CN3.1, CN3.5, CN3.6, CN4.1, CN4.5, CN4.6, CN6.1, CN6.2, CN6.3, CN6.4, CN7.2, CN9.2, CN9.5, D1.2 (A), D2.2 (A), D3.2 (A), D4.1, D5.1, D6.1, D7.1, D8.2 (A), D9.2 (A), D10.2 (A), D11.2 (A), D12.2 (A), D13.2 (A), D14.2, D15.2 (A), D16.2 (A), D17.2 (A), D18.2 (A), D21.1, D22.2 (A), D23.2 (A), D24.2 (A), D25.1, D26.1, D27.1, D28.1, D29.2 (A), D30.2 (A), D31.2 (A), D32.2 (A), D33.2 (A), D34.2 (A), D35.2 (A), D36.2 (A), D37.2 (A), D38.2 (A), D39.2, DC1.2, DC1.3, J1.5 (GND), J1.7 (GND), J1.11 (GNDDetect), J2.1, J2.3, J3.3, J5.1, J5.3, J5.9, J5.11, J5.13, J5.15, J5.17, J5.19, J5.21, J5.23, LED1.1 (K), LED2.2 (K), Module1.1 (GND), Module1.2 (GND), Module1.7 (GND), Module1.8 (GND), Module1.13 (GND), Module1.14 (GND), Module1.22 (GND), Module1.23 (GND), Module1.32 (GND), Module1.33 (GND), Module1.42 (GND), Module1.43 (GND), Module1.52 (GND), Module1.53 (GND), Module1.59 (GND), Module1.60 (GND), Module1.65 (GND), Module1.66 (GND), Module1.71 (GND), Module1.74 (GND), Module1.98 (GND), Module1.107 (GND), Module1.108 (GND), Module1.113 (GND), Module1.114 (GND), Module1.119 (GND), Module1.120 (GND), Module1.125 (GND), Module1.126 (GND), Module1.131 (GND), Module1.132 (GND), Module1.137 (GND), Module1.138 (GND), Module1.144 (GND), Module1.150 (GND), Module1.155 (GND), Module1.156 (GND), Module1.161 (GND), Module1.162 (GND), Module1.167 (GND), Module1.168 (GND), Module1.173 (GND), Module1.174 (GND), Module1.179 (GND), Module1.180 (GND), Module1.185 (GND), Module1.186 (GND), Module1.191 (GND), Module1.192 (GND), Module1.197 (GND), Module1.198 (GND), Q1.2 (S), Q2.2 (S), Q3.4 (G), Q5.2 (S), Q6.2 (S), Q7.2 (S), R2.1, R20.2, R21.2, R34.2, R57.2, R58.2, R74.2, R78.2, R82.2, R83.2, R84.2, R85.2, R86.1, R87.1, R88.1, R89.1, R90.1, RJ1.19 (EH), RJ1.20 (EH), SW1.5 (B4), SW1.6 (B3), SW1.7 (B2), SW1.8 (B1), SW2.3, TP2.1 (1_1), U1.15 (VSS), U1.27 (VSSA), U1.31 (VSS), U1.47 (VSS), U1.63 (VSS), U2.2 (GND), U2.5 (GND), U3.4 (GND), U3.5 (A2), U3.6 (A1), U4.4 (GND), U5.1 (GND), U5.10 (GND), U5.12 (GND), U6.1 (GND), U7.7 (GND), U7.9 (EP), U8.3 (GND), U8.8 (GND), U9.3 (GND), U9.8 (GND), U10.2 (GND), U11.3, U11.8, U12.5 (GND), U12.10 (~OE), U13.37 (EP), U14.3, U14.8, U15.3 (GND), U16.3 (GND), U18.1 (GND1), U18.2 (GND1), U18.9 (AUXIN), U18.10 (GND1), USB1.4 (GND), USB1.8 (GND), USB1.9, USBC1.1 (EH), USBC1.2 (EH), USBC1.3 (EH), USBC1.4 (EH), USBC1.A1B12 (GND), USBC1.B1A12 (GND), X1.2 (GND), X1.4 (GND), X2.2 (GND), X2.4 (GND)
unnamed: C32.1, C33.1, L2.2, R40.1
unnamed: C52.1, R75.1
unnamed: C67.2, R77.2
unnamed: C68.1, RJ1.4 (CT), RJ1.5 (CT)
unnamed: CN2.5, D8.1 (K), R16.2
unnamed: CN2.3, D9.1 (K), R12.2
unnamed: CN2.1, D10.1 (K), R10.2
unnamed: CN2.2, D11.1 (K), R11.2
unnamed: CN2.4, D12.1 (K), R15.2
unnamed: CN2.6, D13.1 (K), R17.2
unnamed: CN4.4, D17.1 (K), R29.2
unnamed: CN4.3, D18.1 (K), R32.2
unnamed: CN5.2, D19.2 (A), Q5.3 (D)
unnamed: D20.1 (K), R37.1
unnamed: H1.2, R23.2
unnamed: H2.1, R25.2
unnamed: H3.2, R92.2
unnamed: H4.2, R93.2
unnamed: LED1.2 (A), R3.2
unnamed: LED2.1 (A), R39.2
unnamed: LED3.2 (K), R67.1
unnamed: LED4.2 (K), R91.1
unnamed: Module1.54 (GPIO4), R71.2
unnamed: Module1.34 (GPIO5), R70.2
unnamed: Module1.30 (GPIO6), R69.2
unnamed: Module1.21 (PI_nLED_Activity), R67.2
unnamed: C18.1, Q1.1 (G), R18.1, R20.1
unnamed: C19.1, Q2.1 (G), R19.1, R21.1
unnamed: Q3.1 (S), Q3.2 (S), Q3.3 (S), Q4.1 (S), Q4.2 (S), Q4.3 (S), R22.1
unnamed: Q4.4 (G), R22.2, SW2.2
unnamed: Q5.1 (G), R33.2
unnamed: C37.1, Q6.1 (G), R55.1, R57.1
unnamed: C38.1, Q7.1 (G), R56.1, R58.1
unnamed: R79.2, RJ1.16
unnamed: R80.1, RJ1.18
unnamed: R81.2, USBC1.A4B9 (VBUS), USBC1.B4A9 (VBUS)
unnamed: R2.2, U1.61 (PB8-BOOT0)
unnamed: R27.2, U4.7 (I03)
unnamed: R30.2, U4.3 (WP#(IO2))
unnamed: R36.2, U5.3 (RXD)
unnamed: R35.2, U5.2 (TXD)
unnamed: C44.2, U6.7 (BST)
unnamed: C48.2, R72.2, R74.1, U6.5 (FB)
unnamed: R73.1, U6.6 (PG)
unnamed: C44.1, L3.1, U6.8 (SW)
unnamed: C50.1, R73.2, U6.4 (VCC)
unnamed: C52.2, U7.1 (BST)
unnamed: C66.1, R77.1, U7.6 (COMP)
unnamed: C58.2, R76.2, R78.1, U7.5 (FB)
unnamed: C65.1, U7.4 (SS)
unnamed: L4.1, R75.2, U7.8 (SW)
unnamed: R82.1, U10.5 (ILIM)
unnamed: U12.7 (HSD1+), U13.31 (USBDP_UP)
unnamed: U12.6 (HSD1-), U13.30 (USBDM_UP)
unnamed: R90.2, U13.25 (HS_IND/CFG_SEL1)
unnamed: R86.2, U13.35 (RBIAS)
unnamed: R87.2, U13.24 (SCL/SMBCLK/CFG_SEL0)
unnamed: R88.2, U13.22 (SDA/SMBBATA/NON_REM1)
unnamed: R89.2, U13.28 (SUSP_IND/LOCAL_PWR/NON_REM0)
unnamed: C76.1, U13.33 (XTALIN/CLKIN), X2.1 (OSC1)
unnamed: C75.1, U13.32 (XTALOUT), X2.3 (OSC2)
unnamed: J2.5, U15.4 (Y)
unnamed: R91.2, U16.4 (Y)
unnamed: C88.2, L5.1, U18.19 (VISOOUT)
unnamed: R83.1, USBC1.A5 (CC1)
unnamed: R84.1, USBC1.B5 (CC2)

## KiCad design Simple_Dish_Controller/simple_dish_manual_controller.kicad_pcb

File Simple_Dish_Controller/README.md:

# Simple-Dish-Controller
Simple controller with toggle switches to move the motors of a satellite dish.

The project is to create a PCB that will control 2 motors that will be used as the azimuth and elevation motors of a satellite dish. The direction will allow controlling simple movement for each motor, forward, reverse, still, all at one set speed.

The project uses Kicad to create the schematic, PCB and BOM.

This project fulfills 2 initiatives:
- Test out motor control
- Master Kicad for future projects
- Be the base for a follow up PCB that will use a Rashberry Pi to control the motors

## Project Overview

This diagram simply shows the function of the project:

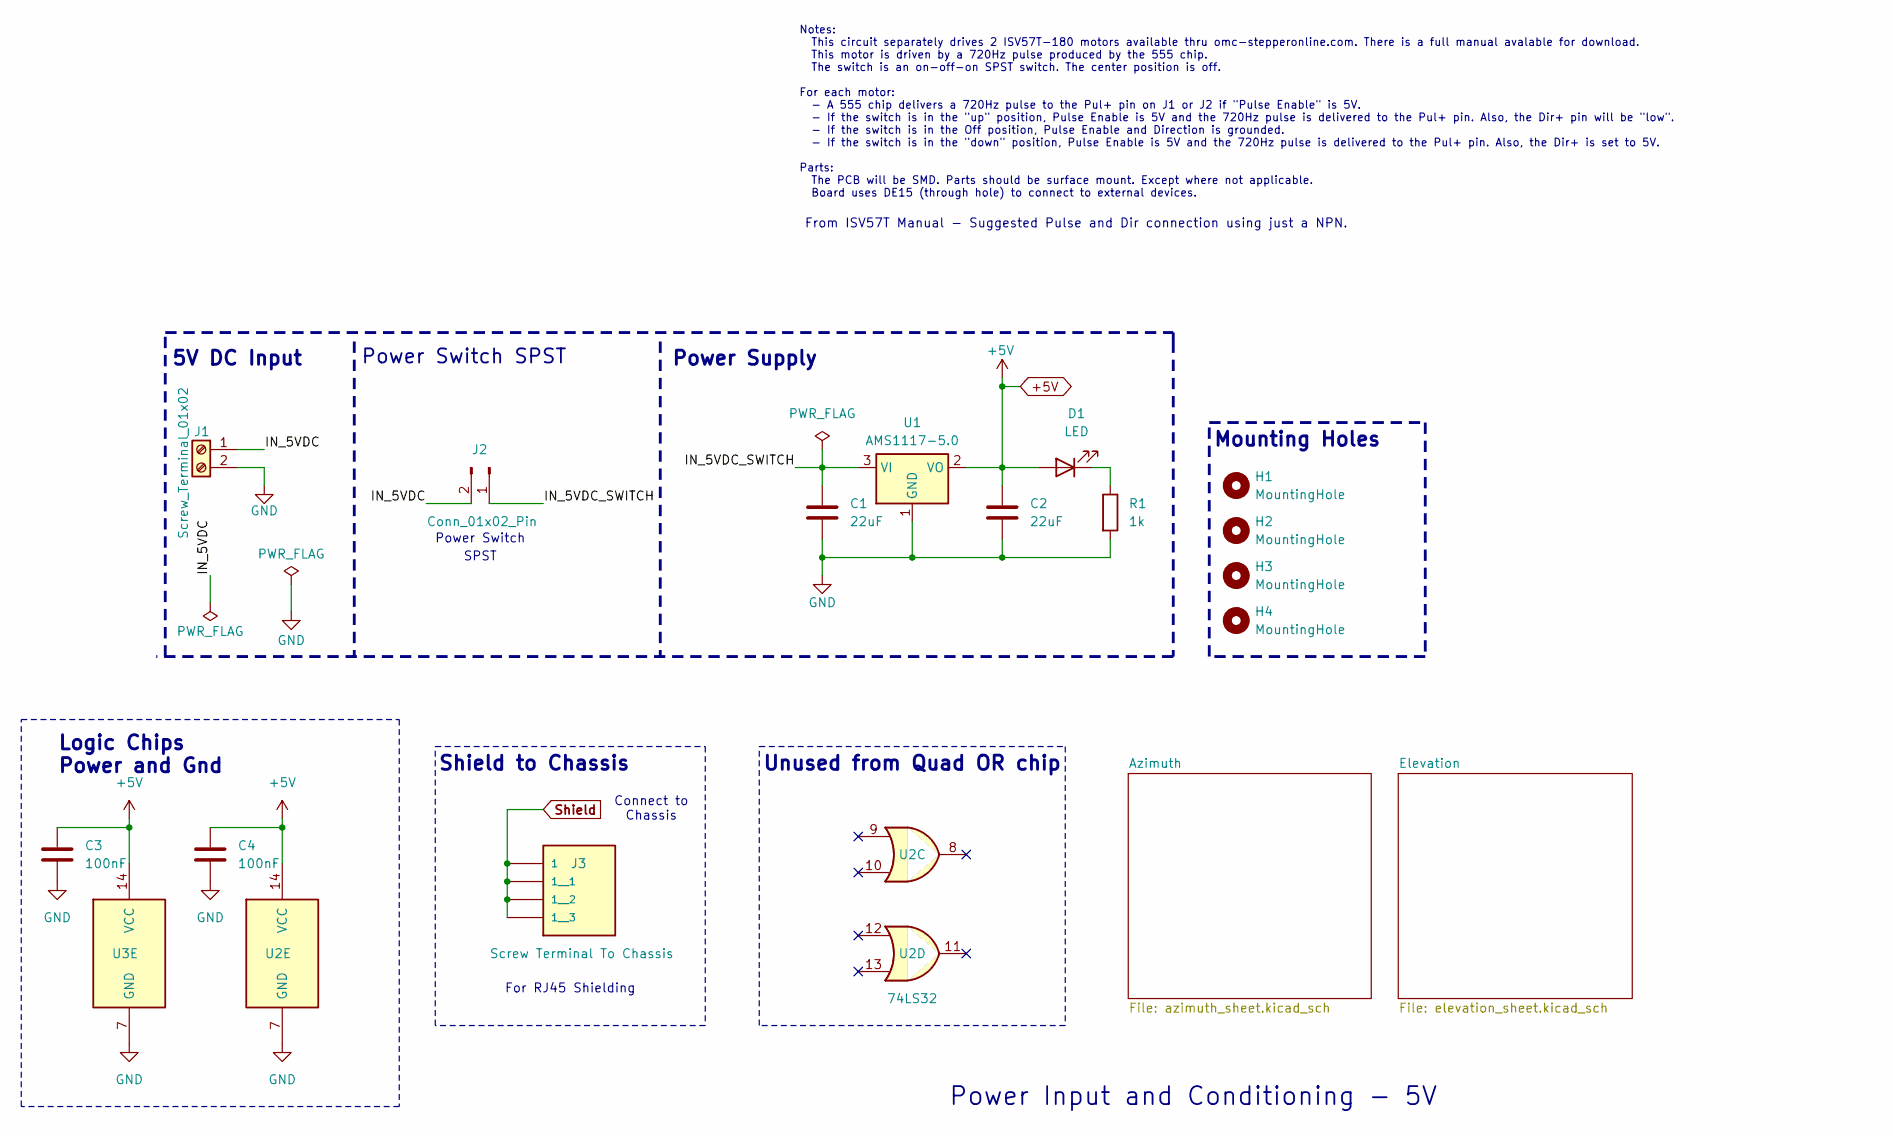
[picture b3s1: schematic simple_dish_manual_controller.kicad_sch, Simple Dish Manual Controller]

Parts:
C1, C2: 22uF; C_1206_3216Metric; LCSC Part C12891
C3, C4: 100nF; C_1206_3216Metric; LCSC Part C24497
D1: LED; LED_1206_3216Metric; LCSC Part C5264252
H1, H2, H3, H4: MountingHole; MountingHole_2.7mm_M2.5
J1: Screw_Terminal_01x02; TerminalBlock_Phoenix_MKDS-1,5-2-5.08_1x02_P5.08mm_Horizont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
J2: Conn_01x02_Pin; PinHeader_1x02_P2.54mm_Vertical
J3: Screw Terminal To Chassis; TERM_SCREW_01x04_VERTICAL_KEYSTONE_7690; PARTREV F
R1: 1k; R_1206_3216Metric; LCSC Part C4410
U1: AMS1117-5.0; SOT-223-3_TabPin2; LCSC Part C6187
U2: 74LS32; SOIC-14_3.9x8.7mm_P1.27mm; LCSC Part C116812
U3: 74LS08; SOIC-14_3.9x8.7mm_P1.27mm; LCSC Part C6802

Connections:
+5V: C2.1, C3.1, C4.1, D1.2 (A), U1.2 (VO), U2.14 (VCC), U3.14 (VCC); also elsewhere on the board
/IN_5VDC: J1.1, J2.2
/IN_5VDC_SWITCH: C1.1, J2.1, U1.3 (VI)
GND: C1.2, C2.2, C3.2, C4.2, J1.2, R1.2, U1.1 (GND), U2.7 (GND), U3.7 (GND); also elsewhere on the board
unnamed: D1.1 (K), R1.1
Shield: J3.1_1 (1), J3.1_2 (1__1), J3.1_3 (1__2), J3.1_4 (1__3); also elsewhere on the board

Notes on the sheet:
For RJ45 Shielding
Power Supply
5V DC Input
SPST
Connect to Chassis
Notes: This circuit separately drives 2 ISV57T-180 motors available thru omc-stepperonline.com. There is a full manual avalable for download. This motor is driven by a 720Hz pulse produced by the 555 chip. The switch is an on-off-on SPST switch. The center position is off. For each motor: - A 555 c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
Unused from Quad OR chip
Shield to Chassis
Logic Chips Power and Gnd
From ISV57T Manual - Suggested Pulse and Dir connection using just a NPN.
Power Switch SPST
Power Input and Conditioning - 5V
Power Switch
Mounting Holes

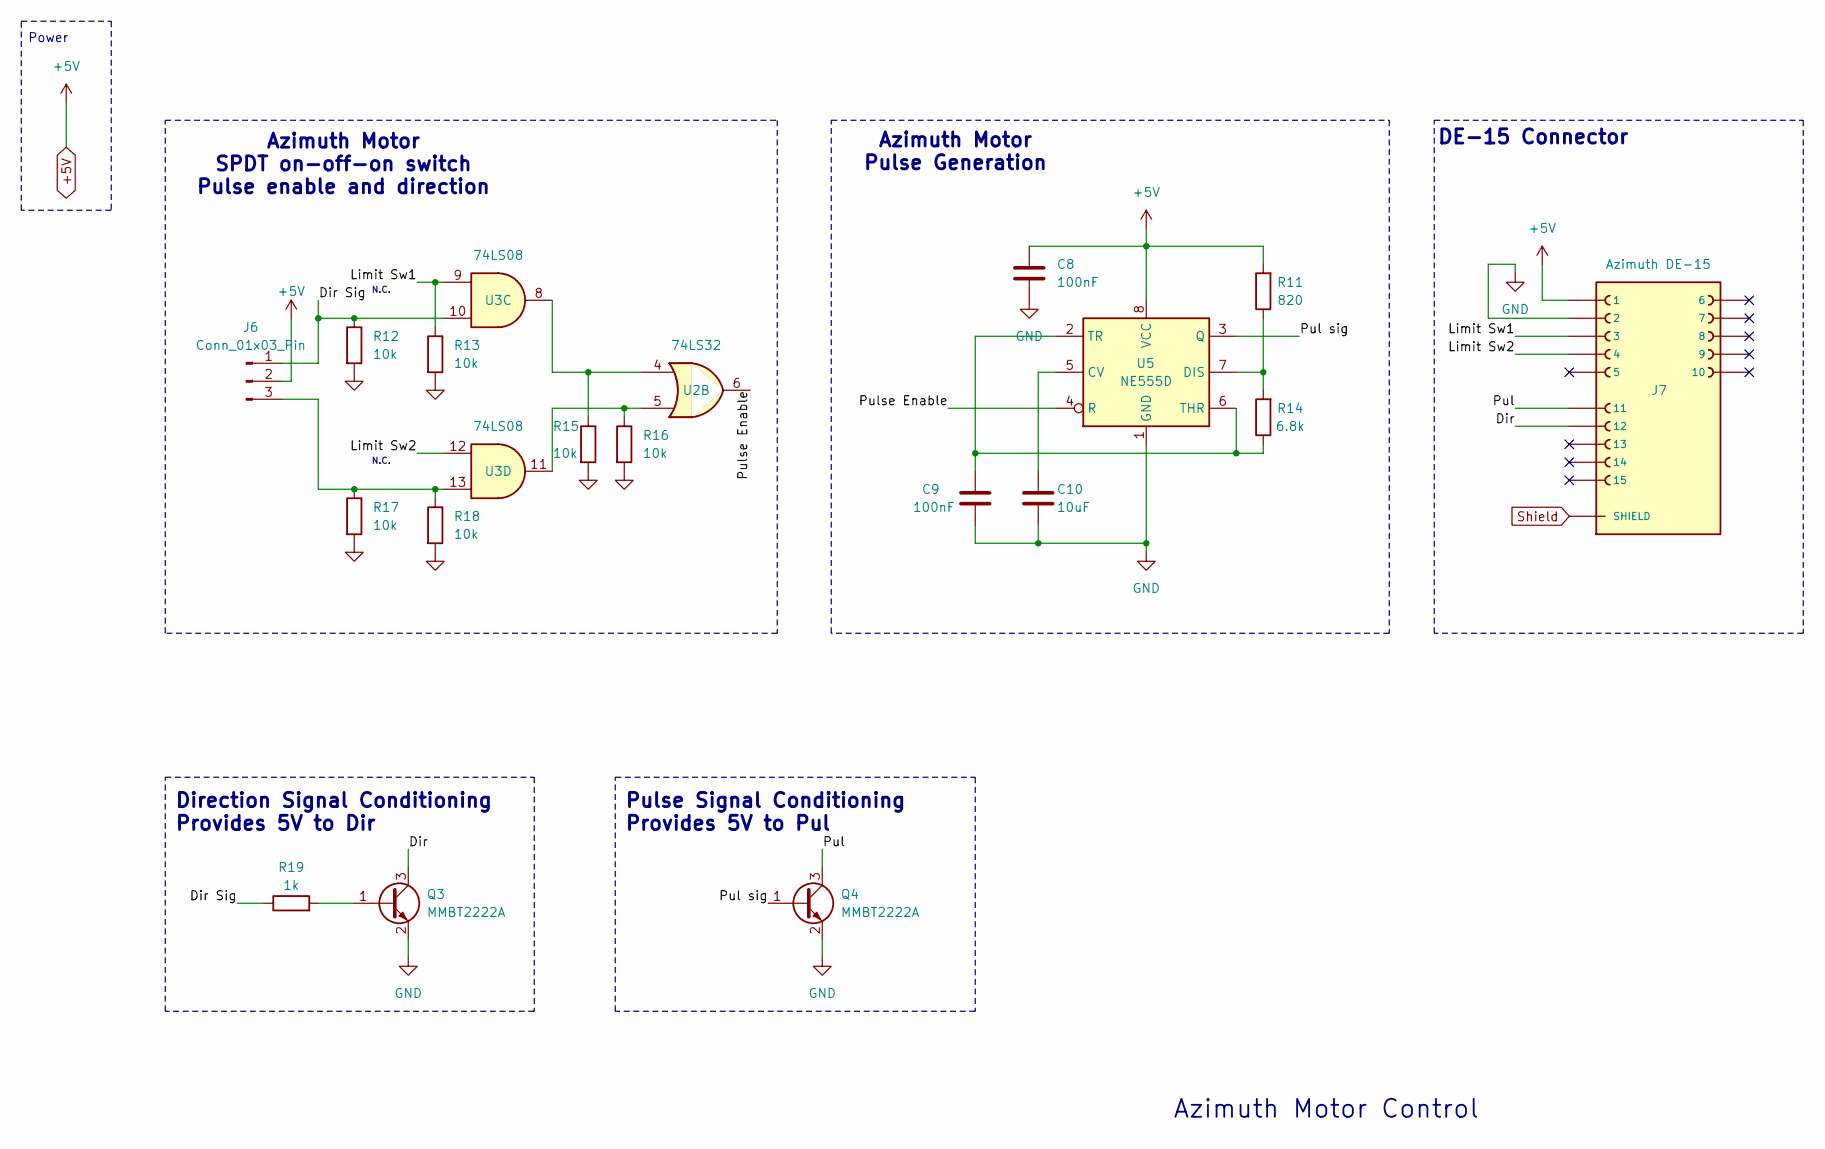
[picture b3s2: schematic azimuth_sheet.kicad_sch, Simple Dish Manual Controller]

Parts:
C8, C9: 100nF; C_1206_3216Metric; LCSC Part C24497
C10: 10uF; C_1206_3216Metric; LCSC Part C13585
J6: Conn_01x03_Pin; PinHeader_1x03_P2.54mm_Vertical
J7: Azimuth DE-15; DE15_VGA_FEMALE_CONN; PARTREV 1; DigiKey_Part_Number L77HDE15SD1CH4FVGA-ND
Q3, Q4: MMBT2222A; SOT-23; LCSC Part C8512
R11: 820; R_1206_3216Metric; LCSC Part C17984
R12, R13, R15, R16, R17, R18: 10k; R_1206_3216Metric; LCSC Part C17902
R14: 6.8k; R_1206_3216Metric; LCSC Part C2907522
R19: 1k; R_1206_3216Metric; LCSC Part C4410
U2: 74LS32; SOIC-14_3.9x8.7mm_P1.27mm; LCSC Part C116812
U3: 74LS08; SOIC-14_3.9x8.7mm_P1.27mm; LCSC Part C6802
U5: NE555D; SOIC-8_3.9x4.9mm_P1.27mm; LCSC Part C234230

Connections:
+5V: C8.1, J6.2, J7.1, R11.2, U5.8 (VCC); also elsewhere on the board
/Azimuth/Dir: J7.12, Q3.3 (C)
/Azimuth/Dir Sig: J6.1, R12.1, R19.1, U3.10
/Azimuth/Limit Sw1: J7.3, R13.1, U3.9
/Azimuth/Limit Sw2: J7.4, U3.12
/Azimuth/Pul: J7.11, Q4.3 (C)
/Azimuth/Pul sig: Q4.1 (B), U5.3 (Q)
/Azimuth/Pulse Enable: U2.6, U5.4 (R)
GND: C8.2, C9.2, C10.2, J7.2, Q3.2 (E), Q4.2 (E), R12.2, R13.2, R15.2, R16.2, R17.2, R18.2, U5.1 (GND); also elsewhere on the board
unnamed: J6.3, R17.1, R18.1, U3.13
unnamed: Q3.1 (B), R19.2
unnamed: R15.1, U2.4, U3.8
unnamed: R16.1, U2.5, U3.11
unnamed: C10.1, U5.5 (CV)
unnamed: R11.1, R14.2, U5.7 (DIS)
unnamed: C9.1, R14.1, U5.2 (TR), U5.6 (THR)
Shield: J7.SH1 (SHIELD), J7.SH2 (SHIELD); also elsewhere on the board

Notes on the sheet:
Azimuth Motor Pulse Generation
Azimuth Motor SPDT on-off-on switch Pulse enable and direction
Azimuth Motor Control
N.C.
Direction Signal Conditioning Provides 5V to Dir
DE-15 Connector
Pulse Signal Conditioning Provides 5V to Pul
Power
